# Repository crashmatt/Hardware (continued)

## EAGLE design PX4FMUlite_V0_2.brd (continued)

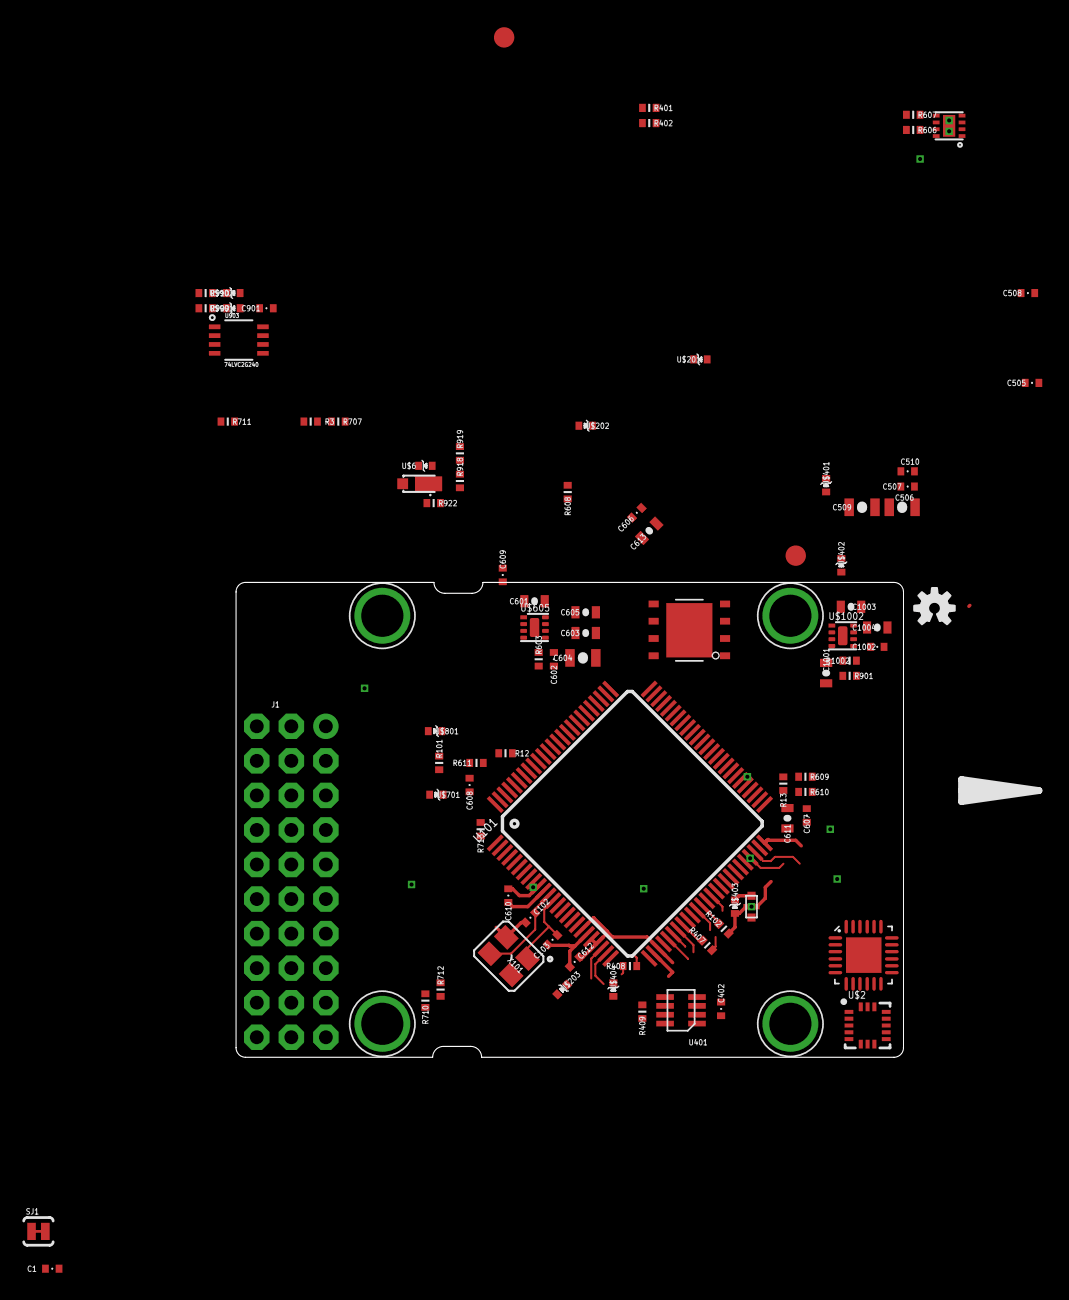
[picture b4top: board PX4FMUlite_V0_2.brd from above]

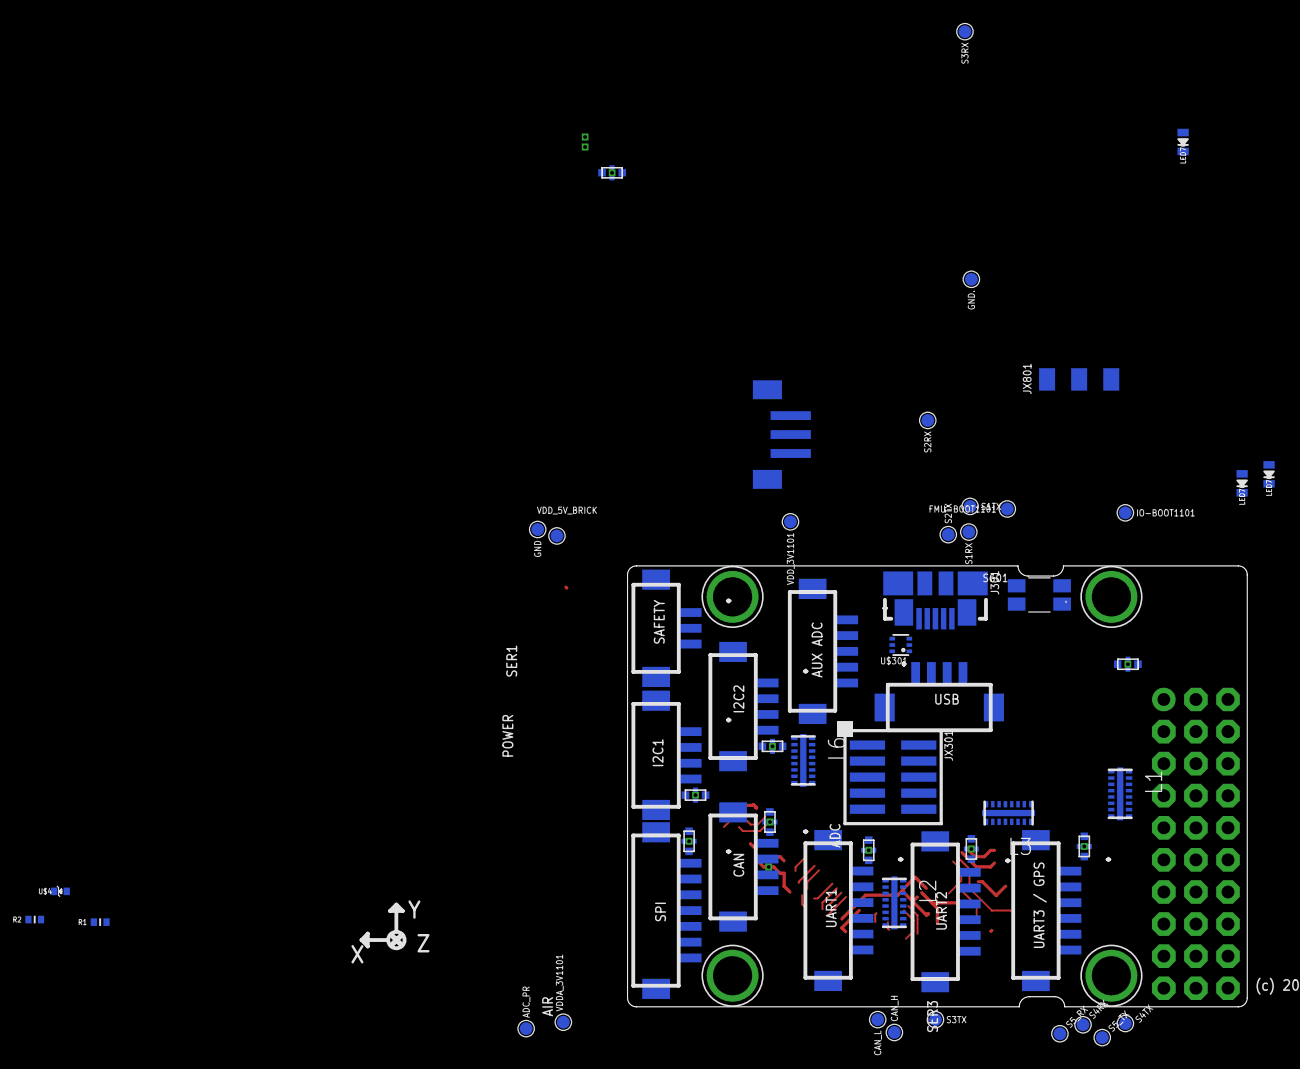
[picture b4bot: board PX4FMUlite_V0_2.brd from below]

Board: 6 copper layers, 49.1 x 34.9 mm, 145 parts (55 on the bottom side), 145 nets.

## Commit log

2013-12-16 added PX4lite - work in progress
2013-12-16 changed PX4FMUlite to from V5 to V0_1
2013-12-16 lots of ripus done on V0_1
2013-12-16 Resize board, resized servo conn plus more
2013-12-17 Removed TXS0105 buffer on excess uarts
2013-12-17 Replaced lvl translators with NFU8042 ESD/EMI filters
2013-12-18 Change to MPU6000 (sparkfun - needs changing), Removed DF13 powerbrick conn
2013-12-18 Added V0_2 because V0_1 would not save
2013-12-18 Changed to winbond W25Q64 64mbit flash in 5*6 8WSON
2013-12-18 Test positioning
2013-12-19 Removed excess UART4/5 connector
2013-12-19 I2C2 connector added.
2013-12-19 General shuffling of filters
2013-12-20 USB connector move to side. UART conns together
2013-12-20 Tweaks on MPU6000
2013-12-20 Moved to V0_3 to make bigger changes
2013-12-20 More tweaks
2013-12-21 Change IO power to 3V3 peripheral power
2013-12-21 Start of isolator-power injector design
2013-12-21 Isolator peripheral side signals done
2013-12-21 Regulator added
2013-12-21 Added TPS62143 buck, moved mounting points
2013-12-21 Changed to MAX21100
2013-12-21 Moved switch plus more tweaks
2013-12-22 Another connector reposition
2013-12-22 Added power input diodes
2013-12-22 Stuff
2013-12-22 Added cap to TPS63031 buck-boost
2013-12-23 Crystal rewire
2013-12-23 buck-boost half wired. CAN wiring in progress.
2013-12-23 Adjusted servo connector direction
2013-12-23 More wiring done
2013-12-23 Hmmm
2013-12-23 Rewired servo ESD a little
2013-12-23 Getting too tight
2013-12-23 Added FMU 3V3 LDO
2013-12-24 LDO shuffle. VBUS reconnected
2013-12-24 USB mostly wired up
2013-12-24 Reconnected VDD_5V_PERIPHERAL
2013-12-24 started to wire MAX21100
2013-12-25 Filter taken from Vin since it is well decoupled through TPS63031
2013-12-25 I2C ESD and VBUS to VIN wired
2013-12-25 Addingsome extra vias to VBUS and GNDs
2013-12-25 More wiring of peripheral 5V power
2013-12-25 Removed SBUS interface that would not fit
2013-12-25 Reworked PPM and spektrum through ESD/filter
2013-12-25 Spektrum 3V3 power routing half done
2013-12-26 Tweaks to FMU 5V LDO layout
2013-12-26 More power routing
2013-12-26 More power routing. flash placed and part routed
2013-12-26 Flash power decoupling
2013-12-26 Sensor LDO routed
2013-12-26 More stuff
2013-12-27 VDD_5V_PERIPH and GND powerplanes added
2013-12-27 Rerouting of 5V_IN to improve V_SERVO routing
2013-12-27 More...
2013-12-27 Fitting pull-up down resistors in
2013-12-27 Moved gps to uart 7 to make room for using timer1/5 for IO
2013-12-27 Added PPM and CH7,9,10 to TIM2&TIM5 pins 22,23,24 etc..
2013-12-27 Added 3v3 power tracks to CAN drivers
2013-12-28 PX4FMULite_V0_4 to remove features that don't fit
2013-12-28 Blue LED removed
2013-12-28 Positioned buckboost Vaux decoupling cap
2013-12-28 Everything fitted before autoroute
2013-12-28 Tweaked power fills to prevent them being isolated after autoroute
2013-12-28 Routed safety switch resistor
2013-12-28 Tweak
2013-12-28 Tweaks tweaks
2013-12-28 More pre-autoroute tweaks
2013-12-28 Moved groundplane flood away from mounting holes
2013-12-28 Voltage sense moved from VSERVO to VAUX
2013-12-28 All clearances and drill distances fixed.
2013-12-28 Removed random track spot outside of dimensions
2013-12-28 Full routed board added
2013-12-29 Moved connector labeling
2013-12-29 Labeling clearup
2013-12-29 Tweaked flood fills to 0.15mm minimum, most 0.2mm
2014-01-04 Added PCB Pool high spec design rules file
2014-01-04 Added PX4Node_mini_V0_1_1
2014-01-04 Removed older generation versions
2014-01-05 Some tweaks
2014-01-06 Tweaks to power and grounds
2014-01-06 Rename to mNode
2014-01-06 Parts renumber
2014-01-06 Sensor 3V3 supply changed to default enabled
2014-01-06 Spektrum 3v3 pulldown resistor moves for better groundplane
2014-01-06 Added spektrum 3V3 enable signal
2014-01-06 Locked connectors
2014-01-06 Moved boot pad to safer position
2014-01-06 More fiddling about
2014-01-06 Modified EP solder paste masks with crosshatch to reduce solder voids
2014-01-06 Removed dull soldering comment
2014-01-06 Renamed and moved some component names
2014-01-06 pre-sbus checkpoint
2014-01-07 Added SBUS input inverter
2014-01-07 Added power selector for PPM/Spektrum/SBUS power output
2014-01-07 Added fiducials to bottom side to support fine pitch packages
2014-01-08 Reworked sbus input to make space for sbus output
2014-01-08 SBUS output fitted
2014-01-09 Shuffled USB ESD protector to make a little more space
2014-01-09 Another autorouter detangle tidyup
2014-01-09 Reworked VBAT pullup to make psace around PSU
2014-01-09 Added schottky diode for VBAT charging
2014-01-09 More untangling
2014-01-09 Reconnected missing UART filtered 5V power
2014-01-09 tweaks
2014-01-09 Graphic shuffle
2014-01-10 Realigned bad autoroute alignment on microcontroller pins
2014-01-10 Part renumbering again
2014-01-10 Moved VDD_3V3_SPEKTRUM_EN to a spare ADC to make space for FMU_CH10
2014-01-10 Patched MAX21100 DRDY to MAG_DRDY
2014-01-10 Clearing a few tracks
2014-01-11 Corrected kyocera filter stop mask on center ground pad
2014-01-11 Added nReset SWD connection to !FMU_RESET
2014-01-11 Moved analog connector pads
2014-01-11 Added extra ground and power connections
2014-01-11 Simplified GYRO_DRDY route
2014-01-11 Stop mask removed from vias
2014-01-11 Tracking simplification around MAX21100
2014-01-11 Cleared more clearance errors
2014-01-11 More clearances cleared
2014-01-11 Renumber
2014-01-11 BOM EXLUDES added to solder jumpers, 0.1" conns etc..
2014-01-11 a few bom tweaks
2014-01-12 Groundplanes added
2014-01-12 Corrected Winbond flash package and added suitable keepout area. Extended top groundplane
2014-01-12 Top groundplane shrunk
2014-01-15 Added uNode, Removed old versions of mNode
2014-01-15 Some uNode first layout
2014-01-15 uNode - Bit more layout
2014-01-16 CAN layout done
2014-01-16 uNode - More layout
2014-01-17 uNode - Just more layout
2014-01-18 Layout UART 1&2
2014-01-18 UART 3 ESD swap
2014-01-18 uNode - Memory layout
2014-01-18 uNode - Lots more layout
2014-01-18 Removed unused 3V3 peripheral power from regulator
2014-01-19 uNode - More pullup resistor placed
2014-01-19 PTH for boot and bat
2014-01-19 uNode - CAN river 3V3 connected
2014-01-20 little tweak
2014-01-20 Changed SBUS inverter for TSSOP part with output enable
2014-01-20 SBUS inverter changed to VSSOP and layout done
2014-01-20 Battery added. Floods added to power tracks
2014-01-20 Groundplane added
2014-01-20 Almost routed
2014-01-21 Servo output channels ripped up for reshuffle
2014-01-21 Layout done
2014-01-21 Much trace tidying and simplification
2014-01-21 More layout cleanup done
2014-01-21 Placement labels arranged
2014-01-22 Nice and tidy
2014-02-02 Added more vias to regulator power paths
2014-02-02 All design rules violations fixed or approved
2014-02-02 Thickened pogo connector traces where possible
2014-02-02 Removed extra Vbat hole
2014-02-02 A little more grounding
2014-02-03 Excluded 0.1" connectors from BOM
2014-02-03 General track thickening
2014-02-03 Final track tweaks
2014-02-03 final final track tweaks
2014-02-03 yet more final track tweaks
2014-02-03 Added PARTNO and EXCLUDE to BOM. Parts renumbered
2014-02-03 More BOM tweaks
2014-02-04 One last track thickening
2014-02-04 PCB component smash and name placement
2015-01-09 Added uNode V0_1_2
2015-01-10 Added PX4uNode_V01_01_3
2015-01-11 Tweaks of uNode_V0_1_3
2015-01-16 Added PX4uNode_v0_2_1 files
